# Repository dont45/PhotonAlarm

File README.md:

# PhotonAlarm
A Cloud based General Alarm system based upon the Particle Photon.
The design intent is to create a small, inexpensive, flexable system to manage a wide range of sensors / detectors and provide alarm system conditioin management via an iPhone or similar device.

The current hardware in proto-type form and this software is currently running in a beta test as a storage shed alarm.  It currently has three sensors, magnetic door switch, motion detector and smoke detector.

The hardware consists of a Particle Photon, a MCP9808 precision thermometer, a DS2482 i2c to 1-wire interface, a pololu 5 volt regulator, and two status LEDs.  The three sensors are connected via the 1-wire bus, and utilize ds2406 switches connected to the actual sensor devices.

The system communicates with the 'system manager' via Pushover notification messages pushed from the Particle Cloud.  The manager communicates to the alarm system via the Particle Cloud function calls.  Currently these calls are initiated with curl but will be integrated into an iPhone management app.  Critical commands such as Disble, Enable and Alarm-State Acknowledge are securely handled via secrets.  A request for a new random 'secred' is made via the management app.  The secret is sent as an alert to the manager's phone.  This secret is then sent back to the PhotonAlarm along with the desired command.  The command is only performed if the secret matches. The secret is used only once, and times out in a few seconds.  This provides a very secure management platform even from web based messages.

The software utilizes the power of the Photon Particle build system which provides a robust c++ development environment.  The system is designed using several c++ classes and utilizes the c++ standard template library for several critical data structures, e.g. std::list for the sensor list and tripped-sensor list, and std::queue for the outgoing messages.

Currently the configuration is generated into the Photon's eeprom vi a hard-coded sensor list (writeTestConfiguration).  A future version will build a new configuration by 1) detection of a master key (1-wire iButton) at reset,  2) scanning the 1-wire bus for devices and creating the device list, and 3) assignment of name and function for each device detected via the iPhone app.  Master keys are created by having two iButton devices present at reset.  This provides a simple three-step initial (or updated) setup process.  1) Create the master keys, 2) Scan for sensors, and 3) Edit the sensor's name and function.

Currently the code contains heavy use of various debug messages via Serial.print which are enabled by a couple of #defines which will ultimately be removed in the future.

D Thompson has demo video of the companion iPhone app on YouTube:

“photonAlarm iPhone app demo” — iPhone app which monitors and manages a photonAlarm system.

Don Thompson
May 14, 2016

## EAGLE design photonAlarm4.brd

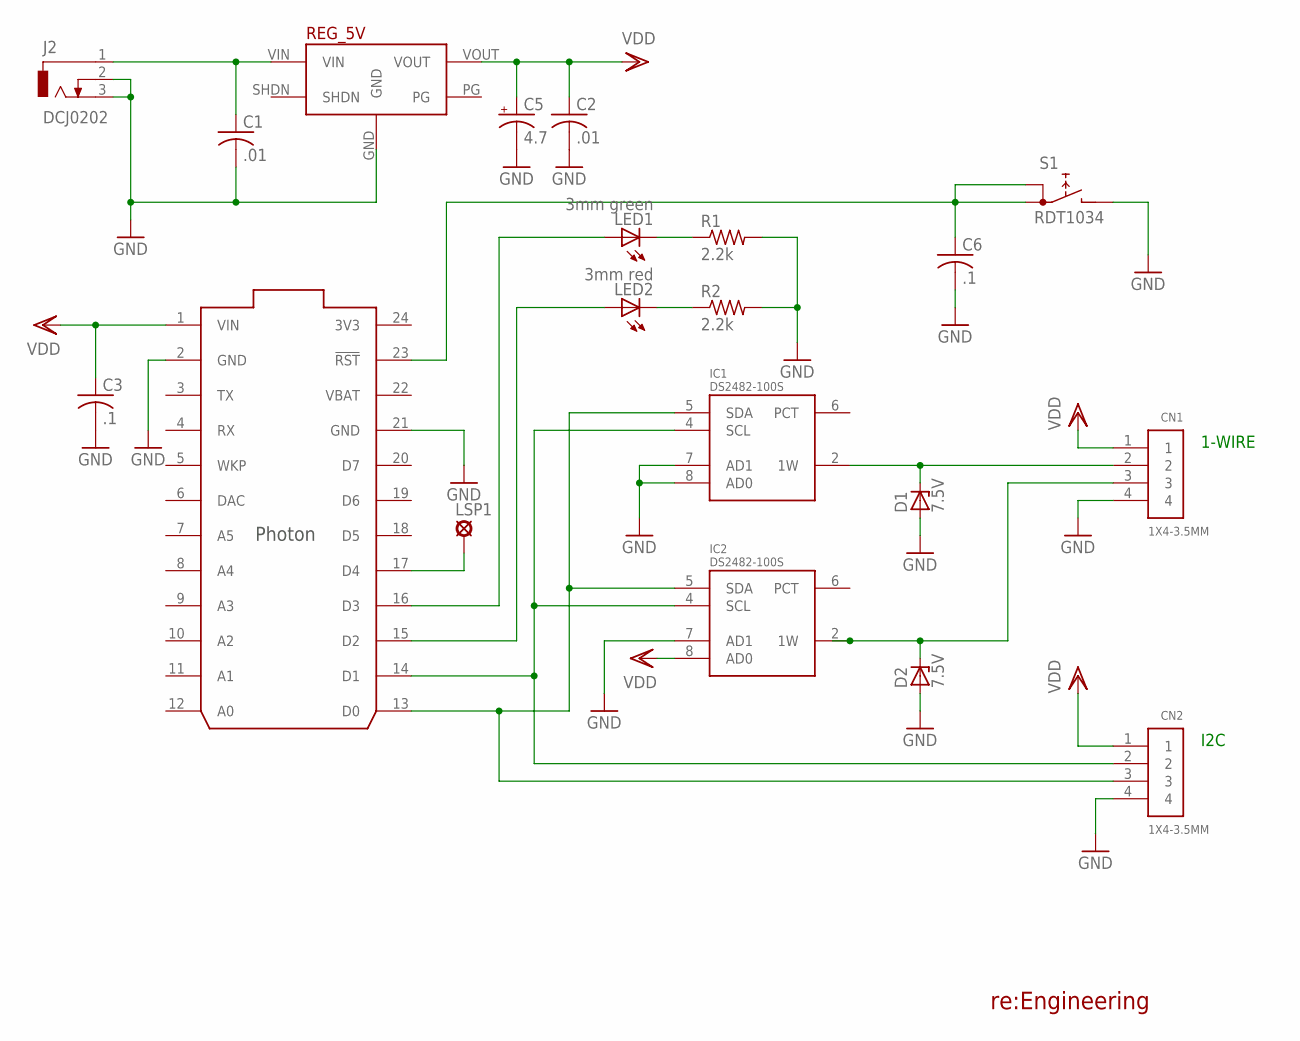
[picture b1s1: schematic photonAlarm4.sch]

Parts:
C1, C2: .01; C0805
C3, C6: .1; C0805
C5: 4.7; E5-6
CN1, CN2: 1X4-3.5MM; 1X04-3.5MM
D1, D2: 7.5V; ZDIO-5
IC1, IC2: DS2482-100S; SO08
J2: DCJ0202
LED1: 3mm green; LED5MM
LED2: 3mm red; LED5MM
LSP1: LSP10
R1, R2: 2.2k; M0805
REG_5V: 5V_D24V10FA; 5V_D24V10F5
S1: RDT1034
U$1: PHOTON_WITH_HEADERS; PHOTON

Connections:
3V3: U$1.24 (3V3)
GND: C1.2, C2.2, C3.2, C5.-, C6.2, CN1.4, CN2.4, D1.A, D2.A, IC1.3 (GND), IC1.7 (AD1), IC1.8 (AD0), IC2.3 (GND), IC2.7 (AD1), J2.2, J2.3, R1.2, R2.2, REG_5V.GND, S1.B, U$1.2 (GND), U$1.21 (GND)
unnamed: LSP1.MP, U$1.17 (D4)
unnamed: CN2.2, IC1.4 (SCL), IC2.4 (SCL), U$1.14 (D1)
unnamed: LED1.K (C), R1.1
unnamed: LED2.K (C), R2.1
unnamed: LED1.A, U$1.16 (D3)
unnamed: LED2.A, U$1.15 (D2)
unnamed: CN2.3, IC1.5 (SDA), IC2.5 (SDA), U$1.13 (D0)
unnamed: CN1.2, D1.C, IC1.2 (1W)
unnamed: CN1.3, D2.C, IC2.2 (1W)
unnamed: C6.1, S1.A, S1.A1, U$1.23 (!RST)
VBAT: U$1.22 (VBAT)
VDD: C2.1, C3.1, C5.+, CN1.1, CN2.1, IC1.1 (VDD), IC2.1 (VDD), IC2.8 (AD0), REG_5V.VOUT, U$1.1 (VIN)
VIN: C1.1, J2.1, REG_5V.VIN

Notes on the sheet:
I2C
1-WIRE
re:Engineering

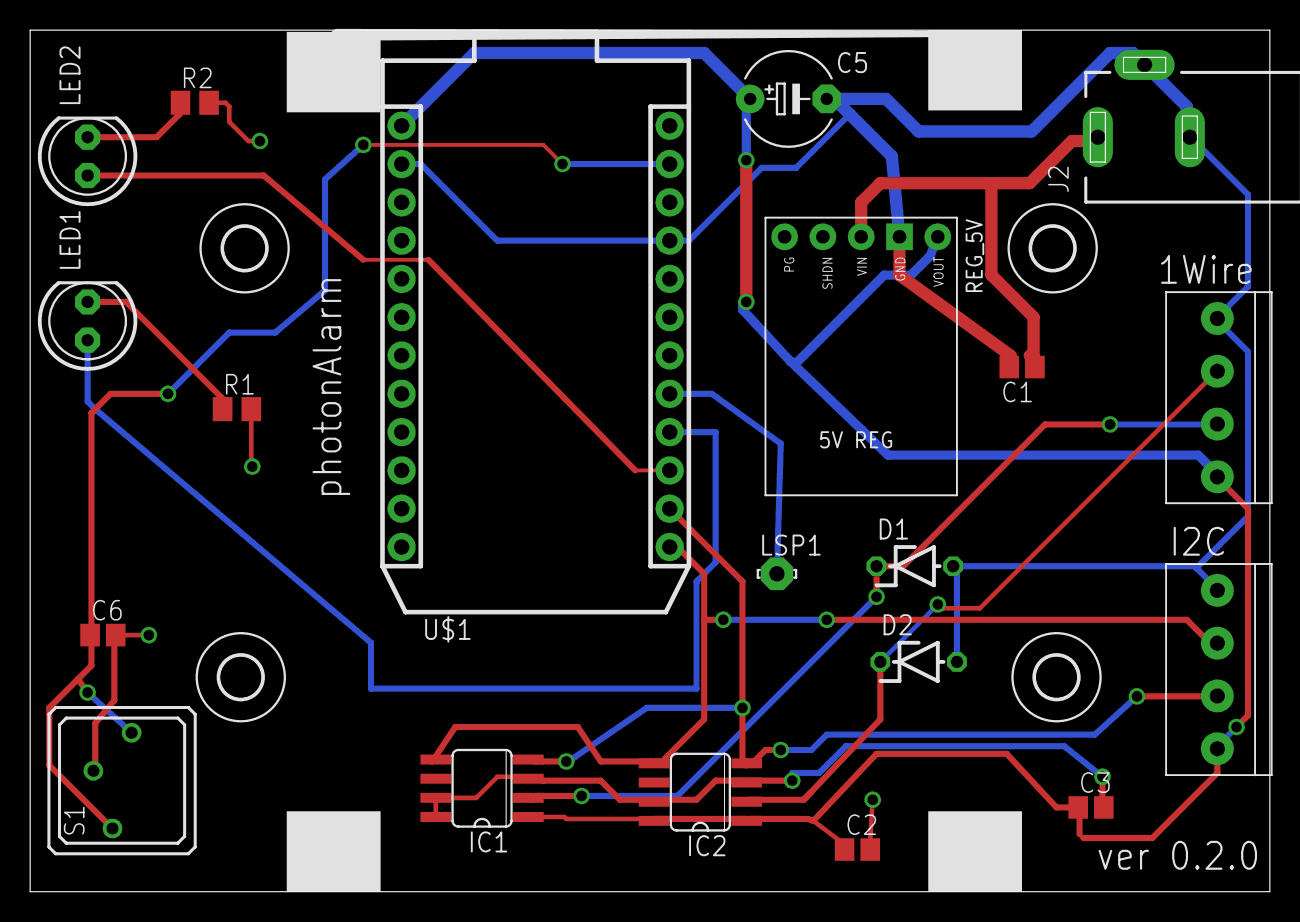
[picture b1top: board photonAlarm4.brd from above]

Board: 2 copper layers, 82.2 x 57.1 mm, 24 parts (0 on the bottom side), 13 nets.

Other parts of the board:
U$2, U$3, U$4, U$5: 2,8

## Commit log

2016-03-06 Added files via upload

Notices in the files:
photonAlarm4.brd:
©2016
